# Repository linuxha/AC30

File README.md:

# SWTPC AC30 Reproduction
A reproduction SWTPC AC-30 Cassette Interface

## Description

I have a couple of Motorola MC6800, MC6802, and MC6809 machines from the 1970's. And I wanted to
setup a typical cassette player/recorder setup to save and load code written on these machines.

**Note:** 2026/10/11 - I hate the way Claude built the human readable schematics. A lot of net lists instead of a nice arrow to the net list. Anyway, so after a bit of double checking I've ordered 5 SMT boards and we'll now see the quality of the designs.

2026/10/11 - The schematics are now drawn with real wires, block by block, instead of a label on every pin. Readable PDFs and PNG images of every sheet and functional block are in [kicad-smt/schematic/](kicad-smt/schematic) (SMT) and [kicad/schematic/](kicad/schematic) (through-hole), for example the SMT modulator:

2026/10/10 - Both boards (through-hole `kicad/AC30` and SMT `kicad-smt/AC30_SMT`) now wire the front panel (switches, LEDs, motor jacks, MIC A/B and EAR A/B jacks) to labeled through-hole wire pads instead of the J1/J2 Molex connectors. Board details are in [AC30-settings.md](AC30-settings.md) and [AC30-SMT-settings.md](AC30-SMT-settings.md); the parts list is [docs/AC30-BOM.md](docs/AC30-BOM.md), with Kicad BOMs in `kicad/AC30-BOM.csv` and `kicad-smt/AC30_SMT-BOM.csv`.

Board sizes are now 173.0 x 126.5 mm (6.8" x 5.0") through-hole and 173.0 x 88.5 mm (6.8" x 3.5") SMT. Gerbers and drill files for both boards are ready for the board house: [kicad/AC30-gerbers.zip](kicad/AC30-gerbers.zip) (through-hole) and [kicad-smt/AC30_SMT-gerbers.zip](kicad-smt/AC30_SMT-gerbers.zip) (SMT, including the top paste layer for a stencil). `kicad/tools/build.sh` regenerates them on every build, or run `kicad/tools/gerbers.sh` (add `smt` for the SMT board).

The SMT board also has a pick-and-place position file, [kicad-smt/AC30_SMT-top-pos.csv](kicad-smt/AC30_SMT-top-pos.csv) (SMD parts only, mm, origin at the board's bottom-left corner), to go with the BOM for an assembly house. The through-hole board's layout was re-placed so a fresh build routes completely again; the build now tries other placements automatically if routing ever comes up short. Both boards now have a GND copper fill on both layers (thermal reliefs on the GND pads, so they're still easy to hand-solder; details in the settings files above), added automatically by the build after routing. The motor and relay lines (MOTOR_1A/1B/2A/2B, RELAY_1/2) now use the same 0.6 mm tracks as the power rails, good for roughly 1.5 A. Known issues, including what to check before ordering boards, are listed in [KNOWN-ISSUES.md](KNOWN-ISSUES.md).

2026/10/09 - I've update the PCB to add the mod/demod circuits and a Molex for the power. Additionally I had a new SMT version created.

2026/10/08 - This is my first go around with Claude, Kicad and FreeCAD and creating a PCB to be sent off as Gerbers. I have a lot of inspecting to do. But for a 1st go this is scary impressive.

## Claude created Kicad files

I gave Claude the following prompts:

```text
Create a kicad schematic for docs/AC30-BOM.md docs/ac30_schematica.jpg
```

and

```text
Save what you have but provide solder pads and labels for the missing power and mod/demod
```

and

```text
Now create the pcb from the schematics. Minimize the board size but leave a safe boarder along the edge.
```

After this I use a few suggested prompts.

Here's what the inside of the Original SWTPC AC30:

I'd estimate the board to be about 9" x 9" (inches) in size. Here's the schematics I gave Claude:

I gave it the [AC30/docs/AC30-BOM.md](BOM) file (simple markdown text file).

Claude started churning and created a 'schematic' (doesn't look like the above, hard to read) and I imported it into the PCB editor. Then didn't make any changes. Instead I let Claude do the rerouting.

I then found out I needed to upgrade Kicad to 10.7 and FreeCAD 26.3 so Claude could create Python 3.11 scripts to build a schematic, the PCB and routing. That was messy as I have Debian Trixie and the latest wants Debian Forky. Anyway, this is the final 1st round attempt. More cleanup to do yet before I ship off the Gerbers.

I'd estimate the size of the new PCB to be about 3.5" x 7" (inches).

So after several hours, including the Kicad/FreeCAD SNAFU, those are the results. The TPx are where I just dumped a bunch of jumpers I hadn't decided on. I'll fix those later. While it's not done it's a huge jump. It would have taken me about two weeks to get all the parts on the schematic, connections defined and PCB routed.

## Credits

I stole this from [Deramp's AC30 (Mike)](https://www.swtpc.com/mholley/ac30/ac30_index.html) site.
And he saved it from Mike Holley's original SWTPC site.

## Links

- [Deramp's AC30 page](https://www.swtpc.com/mholley/ac30/ac30_index.html)

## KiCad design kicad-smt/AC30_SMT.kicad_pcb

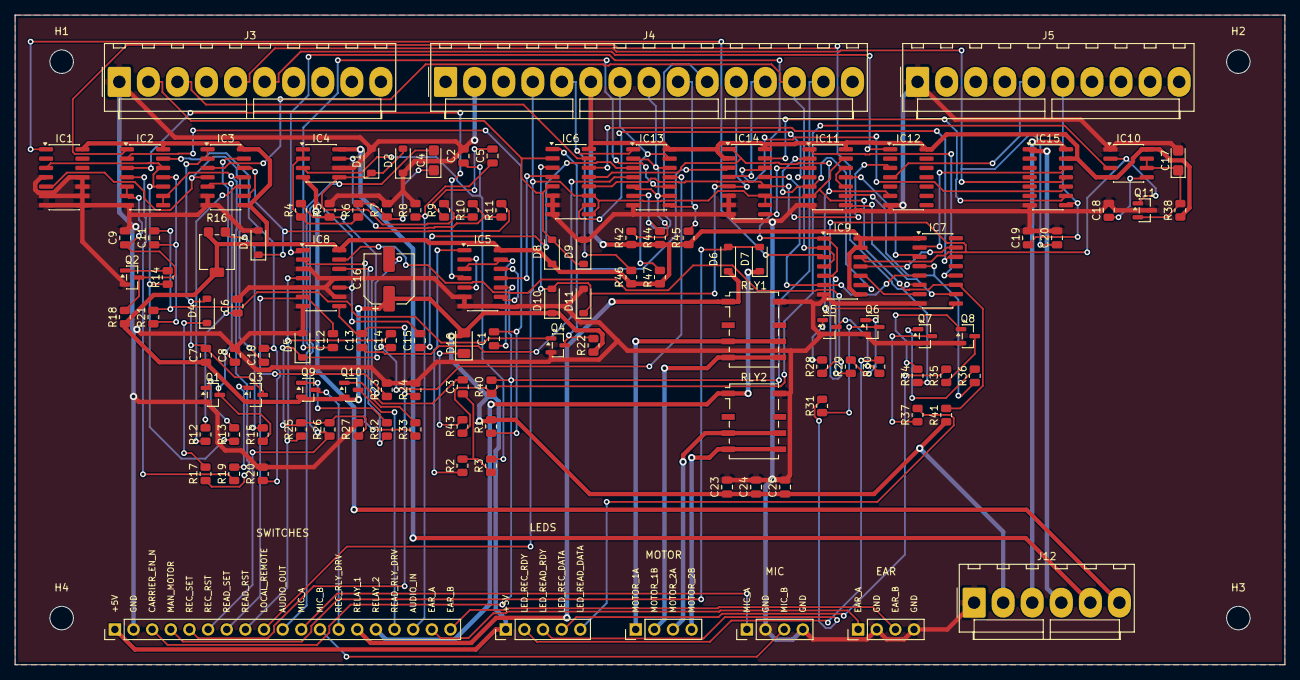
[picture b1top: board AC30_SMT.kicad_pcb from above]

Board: 2 copper layers, 173.0 x 88.5 mm, 122 parts (0 on the bottom side), 121 nets.

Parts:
C1, C6, C12, C13, C14, C15: 1000pF; C_0805_2012Metric
C2: 2000pF; C_0805_2012Metric
C3, C8: 0.022uF; C_0805_2012Metric
C4: 1uF 15V; CP_EIA-3216-18_Kemet-A
C5, C18: 0.01uF; C_0805_2012Metric
C7, C9: 0.047uF; C_0805_2012Metric
C10: 2700pF; C_0805_2012Metric
C11, C19, C20: 470pF; C_0805_2012Metric
C16: 100uF 16V; CP_Elec_6.3x7.7
C17: 10uF 10V tant; CP_EIA-3216-18_Kemet-A
C23, C24, C25: 0.1uF; C_0805_2012Metric
D1, D2, D4, D5, D6, D7, D8, D9, D10, D11: 1N4148W; D_SOD-123
D3: BZT52C4V7 4.7V; D_SOD-123
D18: LED; LED_1206_3216Metric
H1, H2, H3, H4: MountingHole; MountingHole_3.2mm_M3
IC1, IC5, IC8: 4013; SOIC-14_3.9x8.7mm_P1.27mm
IC2, IC11: 4001; SOIC-14_3.9x8.7mm_P1.27mm
IC3, IC13: 4070; SOIC-14_3.9x8.7mm_P1.27mm
IC4: 4558; SOIC-8_3.9x4.9mm_P1.27mm
IC6, IC14: 4053; SOIC-16_3.9x9.9mm_P1.27mm
IC7: 4049; SOIC-16_3.9x9.9mm_P1.27mm
IC9: 4023; SOIC-14_3.9x8.7mm_P1.27mm
IC10: 555; SOIC-8_3.9x4.9mm_P1.27mm
IC12: 1489; SOIC-14_3.9x8.7mm_P1.27mm
IC15: 1488; SOIC-14_3.9x8.7mm_P1.27mm
J1: SWITCHES; PinHeader_1x19_P2.54mm_Vertical
J2: LEDS; PinHeader_1x05_P2.54mm_Vertical
J3: Computer interface (COMP); Molex_KK-396_A-41791-0010_1x10_P3.96mm_Vertical
J4: Control interface; Molex_KK-396_A-41791-0015_1x15_P3.96mm_Vertical
J5: Terminal interface (TERM); Molex_KK-396_A-41791-0010_1x10_P3.96mm_Vertical
J12: Power input; Molex_KK-396_A-41791-0006_1x06_P3.96mm_Vertical
J13: MOTOR; PinHeader_1x04_P2.54mm_Vertical
J14: MIC; PinHeader_1x04_P2.54mm_Vertical
J15: EAR; PinHeader_1x04_P2.54mm_Vertical
Q1, Q2, Q4, Q5, Q6, Q7, Q8: MMBT5088; SOT-23
Q3, Q9, Q10, Q11: MMBT5087; SOT-23
R1: 33K; R_0805_2012Metric
R2, R3, R9, R11, R12, R15, R19, R20, R21, R22, R27, R28, R29, R32, R33, R34, R36, R40, R41, R42, R44, R45, R46, R47: 10K; R_0805_2012Metric
R4: 330; R_0805_2012Metric
R5: 2.2K; R_0805_2012Metric
R6: 4.7K; R_0805_2012Metric
R7, R30, R31, R35, R37, R43: 470; R_0805_2012Metric
R8, R17, R18, R23, R24, R25, R26: 100K; R_0805_2012Metric
R10: 330K; R_0805_2012Metric
R13, R14: 22K; R_0805_2012Metric
R16: 20K trim; Potentiometer_Bourns_3314G_Vertical
R38: 47K; R_0805_2012Metric
RLY1, RLY2: G6K-2F-Y 5V; Relay_DPDT_Omron_G6K-2F-Y

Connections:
+5V: C7.1, C16.1, C23.1, C24.1, C25.1, D8.1, D10.1, D18.2, IC1.14, IC2.14, IC3.8, IC3.14, IC5.14, IC6.16, IC7.1, IC8.14, IC9.8, IC9.13, IC9.14, IC10.4, IC10.8, IC11.14, IC12.14, IC13.14, IC14.2, IC14.16, IC15.13, J1.1, J2.1, J4.6, J12.2, Q3.2, Q9.2, Q10.2, R1.2, R16.2, R16.3, R18.1, R22.1, R38.1, R41.1, R42.1, R44.1, R45.1, R46.1, R47.1
+7.5V: IC4.8, J12.5
+13V: IC15.14, J12.3
-7.5V: IC4.4, J12.6
-13V: IC15.1, J12.4
/CPU_CLK_IN: IC6.15, J3.3
/CPU_CLK_OUT: D8.2, D9.1, IC6.2, IC6.5, J3.2
/CPU_DATA: IC6.12, IC12.3, IC14.12
/CPU_RS232_IN: C20.1, IC15.11, J3.5
/CPU_RS232_OUT: IC12.1, J3.6
/CPU_RX: IC7.2, IC15.12
/CPU_RX_N: IC7.3, IC11.11
/CTRL_INVERT: IC13.2, IC13.5, IC13.9, IC13.12, J4.8, R42.2
/D18_K: D18.1, R43.2
/DATA_SEL: IC6.14, IC7.14
/DATA_SEL_N: IC7.15, IC9.11
/DELAY_OUT: IC10.3, R40.1, R43.1
/DELAY_RC: C17.1, IC10.6, IC10.7, Q11.2, R38.2
/EAR_A: J1.18, J15.1
/EAR_B: J1.19, J15.3
/ECHO_N: IC11.10, IC11.12
/IC10_CV: C18.1, IC10.5
/LED_READ_DATA: J2.5, R37.2
/LED_READ_RDY: J2.3, R31.2
/LED_REC_DATA: J2.4, R35.2
/LED_REC_RDY: J2.2, R30.2
/LOCAL_REMOTE: IC6.9, IC6.11, IC7.11, IC11.6, IC11.13, IC14.10, IC14.11, J1.9, J4.4, R41.2
/MAN_MOTOR: D6.2, D7.2, J1.4
/MIC_A: J1.11, J14.1
/MIC_B: J1.12, J14.3
/MOTOR_1A: J13.1, RLY1.3, RLY1.6
/MOTOR_1B: J13.2, RLY1.4, RLY1.5
/MOTOR_2A: J13.3, RLY2.3, RLY2.6
/MOTOR_2B: J13.4, RLY2.4, RLY2.5
/Mod/Demod & power input/DEM_BIT: C10.1, IC1.5, IC3.4
/Mod/Demod & power input/DEM_BIT_EDGE: C10.2, IC2.13, R20.1
/Mod/Demod & power input/DEM_CD: C7.2, D4.2, IC3.1, IC3.2, Q3.3
/Mod/Demod & power input/DEM_CLK_N: C11.1, IC2.11, R21.1
/Mod/Demod & power input/DEM_CMP: IC4.7, R10.2, R11.1
/Mod/Demod & power input/DEM_D4: D4.1, R17.2
/Mod/Demod & power input/DEM_DLY: C6.1, IC3.13, R12.2
/Mod/Demod & power input/DEM_EDGE: IC2.8, IC2.9, IC3.11, R17.1
/Mod/Demod & power input/DEM_HP: C5.2, R9.1
/Mod/Demod & power input/DEM_IN: D1.1, D2.2, IC4.5, R9.2, R10.1
/Mod/Demod & power input/DEM_INV: IC3.10, R12.1
/Mod/Demod & power input/DEM_LIM: D3.1, IC3.9, IC3.12, R11.2
/Mod/Demod & power input/DEM_PULSE: IC1.3, IC2.10, IC2.12, R13.1, R14.1
/Mod/Demod & power input/DEM_Q1B: Q1.1, R13.2
/Mod/Demod & power input/DEM_Q2B: Q2.1, R14.2
/Mod/Demod & power input/DEM_Q2C: C9.1, IC2.5, IC2.6, Q2.3, R18.2
/Mod/Demod & power input/DEM_Q3B: IC2.4, R19.1
/Mod/Demod & power input/DEM_Q3B_R: Q3.1, R19.2
/Mod/Demod & power input/DEM_Q4B: C11.2, Q4.1, R21.2
/Mod/Demod & power input/DEM_R16: R15.2, R16.1
/Mod/Demod & power input/DEM_TIMER: C8.1, IC3.5, Q1.3, R15.1
/Mod/Demod & power input/MOD_ATTEN: C4.1, R6.2, R7.1
/Mod/Demod & power input/MOD_CLK2: C1.1, IC5.3, IC5.13
/Mod/Demod & power input/MOD_DIV2_N: IC5.9, IC5.12
/Mod/Demod & power input/MOD_DIV4_N: IC5.2, IC5.5
/Mod/Demod & power input/MOD_EDGE: C1.2, IC2.2, R1.1
/Mod/Demod & power input/MOD_F1: C3.1, R2.2, R3.1
/Mod/Demod & power input/MOD_F2: C2.1, IC4.3, R3.2
/Mod/Demod & power input/MOD_FB: C3.2, R4.2, R5.1
/Mod/Demod & power input/MOD_FILT: IC4.1, IC4.2, R4.1, R6.1
/Mod/Demod & power input/MOD_RST: IC2.3, IC5.4
/Mod/Demod & power input/MOD_SQ: IC5.1, R2.1
/POR: C16.2, D5.1, R25.2, R26.2, R27.1
/Q5_B: Q5.1, R28.2
/Q5_C: Q5.3, R30.1
/Q6_B: Q6.1, R29.2
/Q6_C: Q6.3, R31.1
/Q7_B: Q7.1, R36.2
/Q7_C: Q7.3, R37.1
/Q8_B: Q8.1, R34.2
/Q8_C: Q8.3, R35.1
/Q9_B: Q9.1, R32.2
/Q10_B: Q10.1, R33.2
/READ_ACTIVE_N: IC9.9, IC11.2, IC11.5
/READ_EN: IC8.1, IC9.1, IC9.5, R29.1
/READ_EN_N: IC8.2, R33.1
/READ_RLY_DRV: J1.16, Q10.3
/READ_RST: C14.2, IC8.4, J1.8, R25.1
/READ_SET: C12.2, IC8.6, J1.7, R23.1
/REC_DATA_N: IC7.7, IC9.10
/REC_EN: IC8.13, IC9.12, IC10.2, Q11.1, R28.1
/REC_EN_N: IC8.12, R32.1
/REC_RLY_DRV: J1.13, Q9.3
/REC_RST: C15.2, IC8.10, J1.6, R26.1
/REC_SET: C13.2, IC8.8, J1.5, R24.1
/RELAY_1: D6.1, J1.14, RLY1.1
/RELAY_2: D7.1, J1.15, RLY2.1
/REMOTE_N: IC7.12, IC11.1
/SEL_CPU_CLK: IC6.10, IC11.4
/SEL_TERM_CLK: IC11.3, IC14.9
/START_READ: IC13.8, J4.9, R45.2
/START_READ_P: C12.1, IC13.10
/START_RECORD: IC13.6, J4.10, R44.2
/START_REC_P: C13.1, IC13.4
/STOP_READ: IC13.13, J4.7, R47.2
/STOP_READ_P: C14.1, IC13.11
/STOP_RECORD: IC13.1, J4.5, R46.2
/STOP_REC_P: C15.1, IC13.3
/TAPE_DATA: IC7.4, IC11.9, R36.1
/TAPE_DATA_N: IC7.5, IC9.6, IC14.13
/TERM_CLK_IN: IC14.4, J4.12
/TERM_CLK_OUT: D10.2, D11.1, IC6.3, IC14.5, J4.11
/TERM_DATA: IC6.13, IC7.9, IC12.6, IC14.1
/TERM_DATA_N: IC7.10, IC11.8
/TERM_ECHO: IC14.15, IC15.9
/TERM_RS232_IN: C19.1, IC15.8, J5.6
/TERM_RS232_OUT: IC12.4, J5.5
/TERM_TX_SEL: IC14.14, IC15.10
AUDIO_IN: C5.1, J1.17, R8.1
AUDIO_OUT: C4.2, J1.10
CARRIER_DETECT: IC3.3, IC9.2, IC9.4, J4.13
CARRIER_EN_N: IC5.10, J1.3, J4.14, R40.2
CLOCK_IN: IC5.11, IC6.4
CLOCK_OUT: IC6.1, IC14.3, Q4.3, R22.2
DATA_IN: IC2.1, IC7.6, R34.1
DATA_OUT: IC1.1, IC9.3
GND: C2.2, C6.2, C8.2, C9.2, C17.2, C18.2, C19.2, C20.2, C23.2, C24.2, C25.2, D1.2, D2.1, D3.2, D5.2, D9.2, D11.2, IC1.4, IC1.6, IC1.7, IC1.8, IC1.9, IC1.10, IC1.11, IC2.7, IC3.6, IC3.7, IC4.6, IC5.6, IC5.7, IC5.8, IC6.6, IC6.7, IC6.8, IC7.8, IC8.3, IC8.5, IC8.7, IC8.9, IC8.11, IC9.7, IC10.1, IC11.7, IC12.7, IC13.7, IC14.6, IC14.7, IC14.8, IC15.7, J1.2, J3.1, J4.2, J5.1, J12.1, J14.2, J14.4, J15.2, J15.4, Q1.2, Q2.2, Q4.2, Q5.2, Q6.2, Q7.2, Q8.2, Q11.3, R5.2, R7.2, R8.2, R20.2, R23.2, R24.2, R27.2, RLY1.8, RLY2.8

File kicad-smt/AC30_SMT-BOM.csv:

"Reference","Value","Footprint","Qty","Excluded from board"
"C1,C6,C12,C13,C14,C15","1000pF","Capacitor_SMD:C_0805_2012Metric","6",""
"C2","2000pF","Capacitor_SMD:C_0805_2012Metric","1",""
"C3,C8","0.022uF","Capacitor_SMD:C_0805_2012Metric","2",""
"C4","1uF 15V","Capacitor_Tantalum_SMD:CP_EIA-3216-18_Kemet-A","1",""
"C5,C18","0.01uF","Capacitor_SMD:C_0805_2012Metric","2",""
"C7,C9","0.047uF","Capacitor_SMD:C_0805_2012Metric","2",""
"C10","2700pF","Capacitor_SMD:C_0805_2012Metric","1",""
"C11,C19,C20","470pF","Capacitor_SMD:C_0805_2012Metric","3",""
"C16","100uF 16V","Capacitor_SMD:CP_Elec_6.3x7.7","1",""
"C17","10uF 10V tant","Capacitor_Tantalum_SMD:CP_EIA-3216-18_Kemet-A","1",""
"C21","1000uF 25V","","1","Excluded from board"
"C22","100uF 16V","","1","Excluded from board"
"C23,C24,C25","0.1uF","Capacitor_SMD:C_0805_2012Metric","3",""
"D1,D2,D4,D5,D6,D7,D8,D9,D10,D11","1N4148W","Diode_SMD:D_SOD-123","10",""
"D3","BZT52C4V7 4.7V","Diode_SMD:D_SOD-123","1",""
"D12,D13","1N4737 7.5V","","2","Excluded from board"
"D14,D15,D16,D17","1N4003","","4","Excluded from board"
"D18","LED","LED_SMD:LED_1206_3216Metric","1",""
"D19","RECORD RDY","","1","Excluded from board"
"D20","READ RDY","","1","Excluded from board"
"D21","REC DATA","","1","Excluded from board"
"D22","READ DATA","","1","Excluded from board"
"F1","1A","","1","Excluded from board"
"IC1,IC5,IC8","4013","Package_SO:SOIC-14_3.9x8.7mm_P1.27mm","3",""
"IC2,IC11","4001","Package_SO:SOIC-14_3.9x8.7mm_P1.27mm","2",""
"IC3,IC13","4070","Package_SO:SOIC-14_3.9x8.7mm_P1.27mm","2",""
"IC4","4558","Package_SO:SOIC-8_3.9x4.9mm_P1.27mm","1",""
"IC6,IC14","4053","Package_SO:SOIC-16_3.9x9.9mm_P1.27mm","2",""
"IC7","4049","Package_SO:SOIC-16_3.9x9.9mm_P1.27mm","1",""
"IC9","4023","Package_SO:SOIC-14_3.9x8.7mm_P1.27mm","1",""
"IC10","555","Package_SO:SOIC-8_3.9x4.9mm_P1.27mm","1",""
"IC12","1489","Package_SO:SOIC-14_3.9x8.7mm_P1.27mm","1",""
"IC15","1488","Package_SO:SOIC-14_3.9x8.7mm_P1.27mm","1",""
"IC16","7805","","1","Excluded from board"
"J1","SWITCHES","Connector_PinHeader_2.54mm:PinHeader_1x19_P2.54mm_Vertical","1",""
"J2","LEDS","Connector_PinHeader_2.54mm:PinHeader_1x05_P2.54mm_Vertical","1",""
"J3","Computer interface (COMP)","Connector_Molex:Molex_KK-396_A-41791-0010_1x10_P3.96mm_Vertical","1",""
"J4","Control interface","Connector_Molex:Molex_KK-396_A-41791-0015_1x15_P3.96mm_Vertical","1",""
"J5","Terminal interface (TERM)","Connector_Molex:Molex_KK-396_A-41791-0010_1x10_P3.96mm_Vertical","1",""
"J6","MIC A","","1","Excluded from board"
"J7","MIC B","","1","Excluded from board"
"J8","EAR A","","1","Excluded from board"
"J9","EAR B","","1","Excluded from board"
"J10","MOTOR A","","1","Excluded from board"
"J11","MOTOR B","","1","Excluded from board"
"J12","Power input","Connector_Molex:Molex_KK-396_A-41791-0006_1x06_P3.96mm_Vertical","1",""
"J13","MOTOR","Connector_PinHeader_2.54mm:PinHeader_1x04_P2.54mm_Vertical","1",""
"J14","MIC","Connector_PinHeader_2.54mm:PinHeader_1x04_P2.54mm_Vertical","1",""
"J15","EAR","Connector_PinHeader_2.54mm:PinHeader_1x04_P2.54mm_Vertical","1",""
"P1","120 VAC line cord","","1","Excluded from board"
"Q1,Q2,Q4,Q5,Q6,Q7,Q8","MMBT5088","Package_TO_SOT_SMD:SOT-23","7",""
"Q3,Q9,Q10,Q11","MMBT5087","Package_TO_SOT_SMD:SOT-23","4",""
"R1","33K","Resistor_SMD:R_0805_2012Metric","1",""
"R2,R3,R9,R11,R12,R15,R19,R20,R21,R22,R27,R28,R29,R32,R33,R34,R36,R40,R41,R42,R44,R45,R46,R47","10K","Resistor_SMD:R_0805_2012Metric","24",""
"R4","330","Resistor_SMD:R_0805_2012Metric","1",""
"R5","2.2K","Resistor_SMD:R_0805_2012Metric","1",""
"R6","4.7K","Resistor_SMD:R_0805_2012Metric","1",""
"R7,R30,R31,R35,R37,R43","470","Resistor_SMD:R_0805_2012Metric","6",""
"R8,R17,R18,R23,R24,R25,R26","100K","Resistor_SMD:R_0805_2012Metric","7",""
"R10","330K","Resistor_SMD:R_0805_2012Metric","1",""
"R13,R14","22K","Resistor_SMD:R_0805_2012Metric","2",""
"R16","20K trim","Potentiometer_SMD:Potentiometer_Bourns_3314G_Vertical","1",""
"R38","47K","Resistor_SMD:R_0805_2012Metric","1",""
"R48,R49","330","","2","Excluded from board"
"RLY1,RLY2","G6K-2F-Y 5V","Relay_SMD:Relay_DPDT_Omron_G6K-2F-Y","2",""
"S1","AUTO/MAN","","1","Excluded from board"
"S2","RECORD A/B","","1","Excluded from board"
"S3","PLAY A/B","","1","Excluded from board"
"S4","RECORD ON/OFF","","1","Excluded from board"
"S5","READER ON/OFF","","1","Excluded from board"
"S6","POWER (SPDT, one throw used)","","1","Excluded from board"
"S7","LOCAL/REMOTE","","1","Excluded from board"
"T1","120/240V : 18VAC CT 300mA","","1","Excluded from board"
